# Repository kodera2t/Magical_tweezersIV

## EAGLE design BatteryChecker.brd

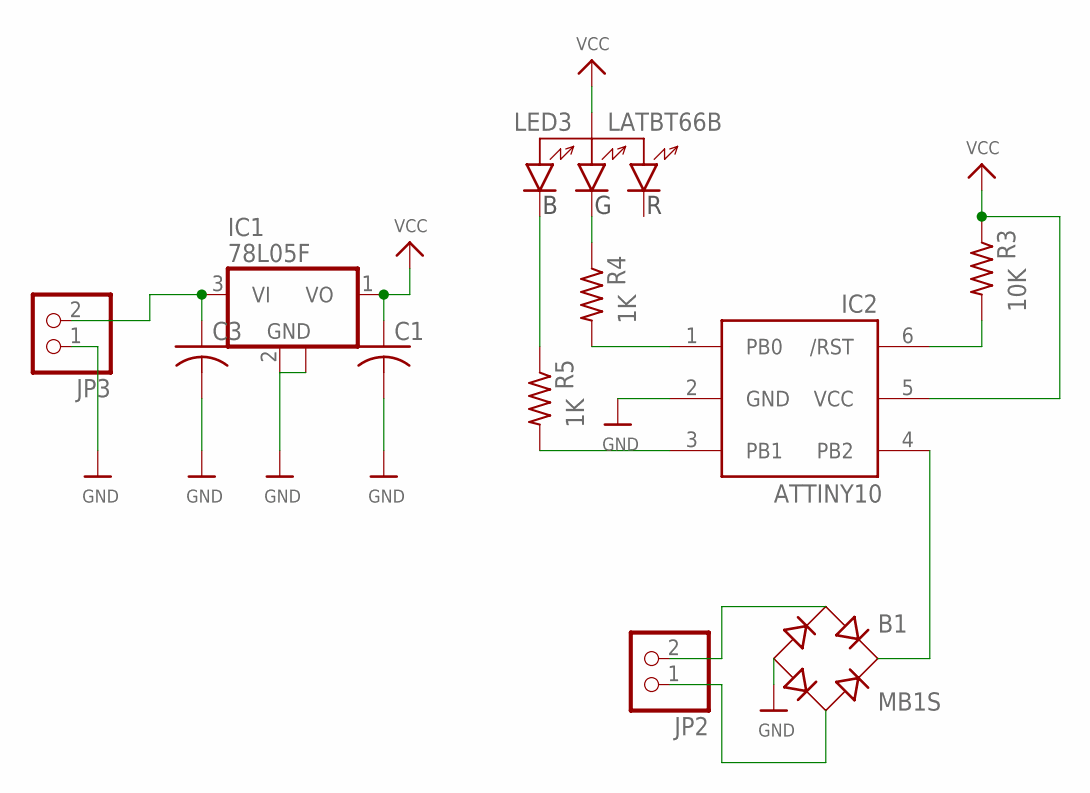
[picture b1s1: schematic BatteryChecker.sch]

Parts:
B1: MB1S; SOIC-4
C1, C3: C-USC0603; C0603
IC1: 78L05F; SOT89
IC2: ATTINY10; SOT23-6
JP2, JP3: HEADER-1X2; 1X02_OVAL
LED3: LATBT66B; P-LCC-4
R3, R4, R5: R-US_R0603; R0603

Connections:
GND: B1.-, C1.2, C3.2, IC1.2 (GND), IC1.2@1 (GND), IC2.2 (GND), JP3.1
unnamed: B1.+, IC2.4 (PB2)
unnamed: LED3.P$4, R4.1
unnamed: IC2.1 (PB0), R4.2
unnamed: C3.1, IC1.3 (VI), JP3.2
unnamed: IC2.6 (/RST), R3.2
unnamed: IC2.3 (PB1), R5.2
unnamed: LED3.P$3, R5.1
unnamed: B1.~1 (AC1), JP2.2
unnamed: B1.~2 (AC2), JP2.1
VCC: C1.1, IC1.1 (VO), IC2.5 (VCC), LED3.P$2, R3.1

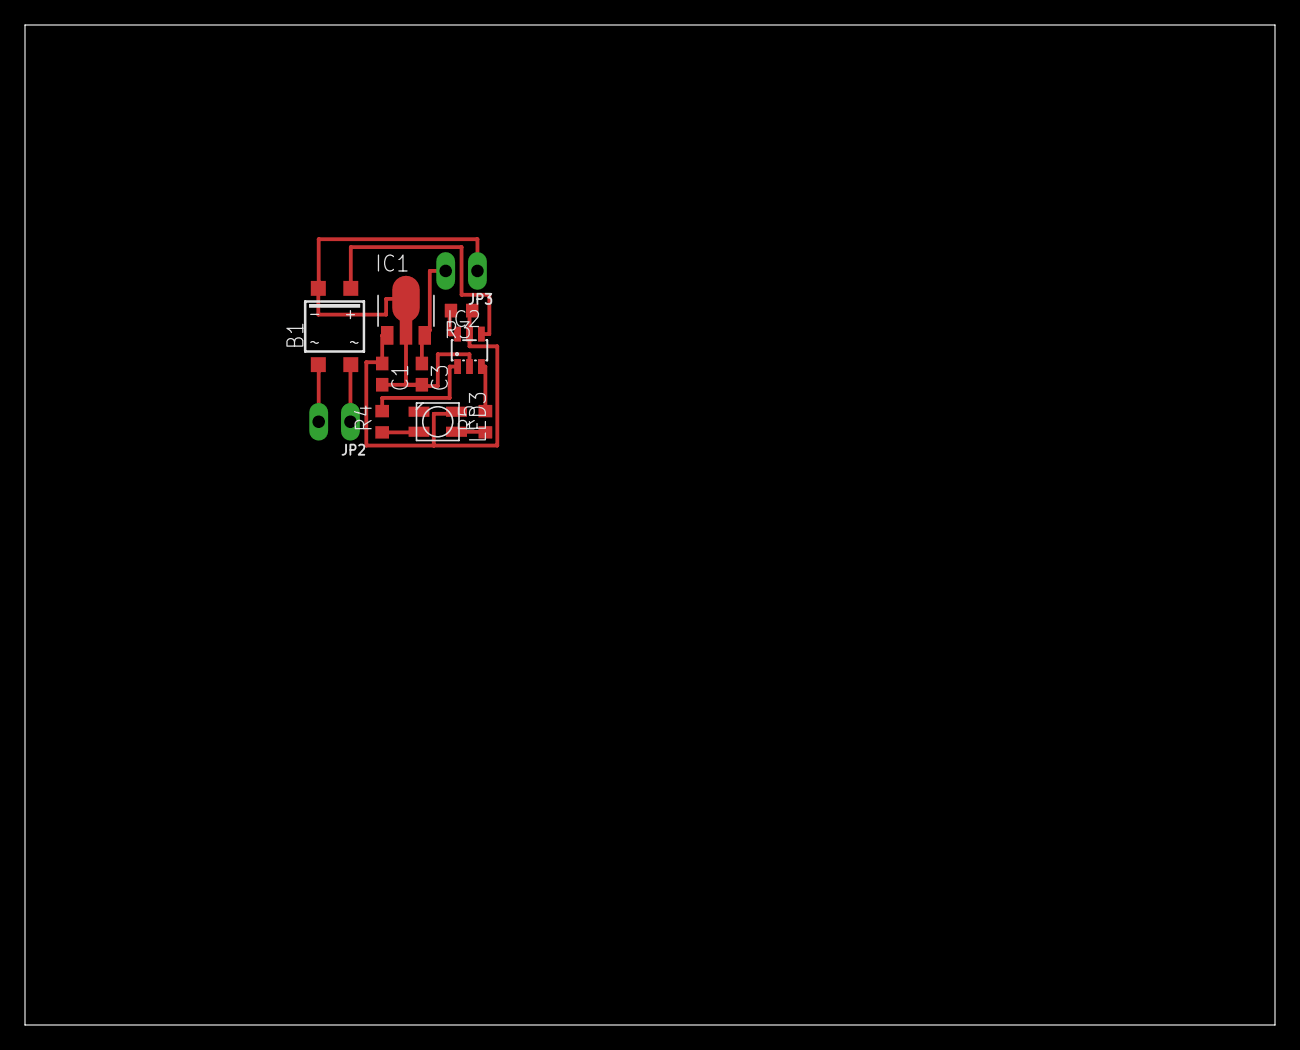
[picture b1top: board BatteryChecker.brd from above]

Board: 2 copper layers, 100.0 x 80.0 mm, 11 parts (0 on the bottom side), 11 nets.

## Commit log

2016-05-28 initial submission
2016-06-16 bitbang at Attiny10
2016-06-18 ATtiny10with I2C and A/D
2016-06-19 super simple frequency counter
2016-06-21 ATTiny10 frequency and voltage multifunction meter

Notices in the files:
parts and their libraries:
OLED_mod: This work is placed in the public domain, and may be freely used for commercial and non-commercial work with the following conditions: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
